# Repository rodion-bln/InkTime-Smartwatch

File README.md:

#  InkTime v6 - Smartwatch Project

**InkTime v6** este un ceas inteligent ultra-low-power, optimizat pentru eficiență și dimensiuni reduse. Proiectul utilizează un procesor nRF52840 și un ecran E-Ink de 1.54 inch, fiind capabil de o autonomie extinsă datorită managementului energetic avansat.

-----

## Diagrama Bloc a Sistemului

```mermaid
flowchart TD
    subgraph PCB_InkTime_v6 [InkTime v6 - 2D Layout Map]
        direction TB

        subgraph Top_Edge [Marginea de Sus - Alimentare]
            USB_C[Port USB-C]
            BAT_PADS[Pad-uri Baterie Li-Po]
            PMIC[Circuit Incarcare BQ25180]
        end

        %% Centrul Plăcii
        subgraph Center_Area [Nucleu Central]
            MCU[nRF52840 SoC]
            XTAL[Oscilatoare 32MHz / 32kHz]
        end

        subgraph Left_Side [Interfata Vizuala]
            DISPLAY_FPC[Conector Display FPC]
            V_REG[Regulator RT6160]
        end

        subgraph Right_Side [Comunicatii RF]
            ANT[Antena Chip Johanson]
            MATCH[Circuit Matching RF]
        end

        subgraph Bottom_Edge [Interfata Programare si Haptic]
            SWD[Pad-uri SWD / Tag-Connect]
            HAPTIC[Driver Haptic + Motor]
            TP_SDA[TP SDA]
            TP_SCL[TP SCL]
        end

        USB_C --> PMIC
        PMIC <--> BAT_PADS
        PMIC --> V_REG --> MCU
        
        MCU -- SPI --> DISPLAY_FPC
        MCU -- I2C --> HAPTIC
        MCU -- I2C --> TP_SDA
        MCU -- I2C --> TP_SCL
        
        MCU -- Traseu 50 Ohm --> MATCH --> ANT
        SWD <--> MCU
        XTAL --- MCU
    end

    %% Stiluri pentru a potrivi vizual cu imaginea
    style MCU fill:#d11,stroke:#333,stroke-width:2px,color:#fff
    style PCB_InkTime_v6 fill:#37474f,stroke:#fff,stroke-width:2px,color:#fff
    style ANT fill:#000,stroke:#f00,color:#fff
    style USB_C fill:#999,stroke:#333
    style SWD fill:#fbc02d,stroke:#333
    style DISPLAY_FPC fill:#546e7a,stroke:#fff,color:#fff
```
-----

## Bill of Materials (BOM) - Componente Cheie

| Componentă | Descriere | Pachet | Link (CSE/SnapEDA) |
| :--- | :--- | :--- | :--- |
| **nRF52840** | Microcontroller BT 5.0 | aQFN-73 | [SnapEDA](https://www.snapeda.com/parts/NRF52840-QIAA-R/Nordic%20Semiconductor/view-part/) |
| **BQ25180** | Battery Charger IC | WLCSP-8 | [CSE](https://componentsearchengine.com/search?term=BQ25180) |
| **MAX17048** | Fuel Gauge (ModelGauge) | WLP-8 | [CSE](https://componentsearchengine.com/search?term=MAX17048) |
| **RT6160** | Buck-Boost Converter | WL-CSP-15 | [CSE](https://componentsearchengine.com/search?term=RT6160) |
| **DRV2605L** | Haptic Driver | VSSOP-10 | [CSE](https://componentsearchengine.com/search?term=DRV2605L) |
| **E-Paper Display Connector** | 1.54" V2 Display | FPC-24 | [CSE](https://componentsearchengine.com/search?term=5034802400) |
| **2450AT** | Antenă Ceramică Chip | 3.2x1.6mm | [CSE](https://componentsearchengine.com/search?term=2450AT18B100E) |

-----

## Descrierea Funcționalității Hardware

### 1\. Sistemul de Procesare (nRF52840)

Utilizăm arhitectura **ARM Cortex-M4F** la **$64\text{ MHz}$**. Alegerea acestui MCU a fost dictată de suportul nativ pentru **USB 2.0** și stack-ul Bluetooth de joasă energie. Comunică cu display-ul prin **SPI** (frecvență de până la $8\text{ MHz}$) și cu restul perifericelor prin **I2C**.

### 2\. Managementul Energiei (Power Path)

  * **Buck-Boost (RT6160):** Asigură o tensiune stabilă de **$3.3\text{V}$** indiferent dacă bateria este la $4.2\text{V}$ (plină) sau scade la $3.0\text{V}$. Acest lucru previne "flicărirea" ecranului sau deconectarea Bluetooth-ului.
  * **Fuel Gauge (MAX17048):** Monitorizează starea bateriei fără a necesita o rezistență de șunt, economisind spațiu și energie.
  * **Consum estimat:**
      * **Deep Sleep:** $\approx 2.5\text{ µA}$
      * **Refresh Ecran:** $\approx 25\text{ mA}$ (timp de 2 secunde)
      * **Autonomie (150mAh):** Aproximativ **18 zile** (cu 10 refresh-uri/zi și conexiune BT intermitentă).

### 3\. Interfață și Feedback

  * **E-Paper:** Tehnologia bi-stabilă permite păstrarea imaginii pe ecran cu **consum zero**.
  * **Haptic Driver (DRV2605L):** Oferă feedback tactil configurabil prin I2C.

-----

## Maparea Pinilor nRF52840

| Pin MCU | Funcție | Componentă | Explicație |
| :--- | :--- | :--- | :--- |
| **P0.26 / P0.27** | SDA / SCL | I2C Bus | Magistrală comună pentru MAX17048, BQ25180, DRV2605. |
| **P0.20** | SCK | SPI Display | Ceasul pentru transferul datelor de imagine. |
| **P0.22** | MOSI | SPI Display | Master Out Slave In - datele către controllerul ecranului. |
| **P0.24** | CS | SPI Display | Chip Select pentru activarea ecranului. |
| **P0.15** | BUSY | Input | Semnal de la ecran către MCU când operația de refresh e gata. |
| **P0.00 / P0.01** | XL1 / XL2 | Cristal 32kHz | Furnizează baza de timp precisă pentru RTC în sleep. |
| **VBUS / D+ / D-** | USB Data | USB-C | Programare, debug și încărcare baterie. |

-----

## Design Log & Decizii de Implementare

### 1\. Decizia privind Vias (Overlap la Pini)

În zona procesorului **nRF52840 (aQFN73)**, am acceptat mici **erori de overlap (suprapuneri)** între vias și pad-urile pinilor.

  * **Justificare:** Densitatea extremă a pinilor nu permitea rutarea standard fără a trece la tehnologii costisitoare de tip *Blind/Buried Vias* sau *Via-in-Pad*. Suprapunerea a fost calculată pentru a asigura continuitatea electrică fără a compromite integritatea structurală a pad-ului în timpul lipirii industriale. Aceasta a permis rutarea pe un PCB standard de **4 straturi**.

### 2\. Integritatea Semnalului (Stackup)

  * S-a implementat un **plan de masă solid (Solid GND)** pe Layer 15.
  * **Decizie:** Nu s-au rutat semnale prin Layer 15 pentru a evita crearea de "antene" accidentale și pentru a oferi o cale de întoarcere curată pentru semnalul RF de $2.4\text{GHz}$.

### 3\. Mecanică și 3D

  * Utilizarea conectorului **TC2030 (Tag-Connect)** pentru a elimina mufa de programare de pe placă, reducând înălțimea totală a ceasului cu **$2\text{ mm}$**.

-----

## Structura Proiectului

  * `/Hardware`: Scheme (.fsch) și Board (.fbrd).
  * `/Manufacturing`: Gerbers.zip
  * `/Mechanical`: Fișier STEP și Carcasa.
  * `/Images`: Randări

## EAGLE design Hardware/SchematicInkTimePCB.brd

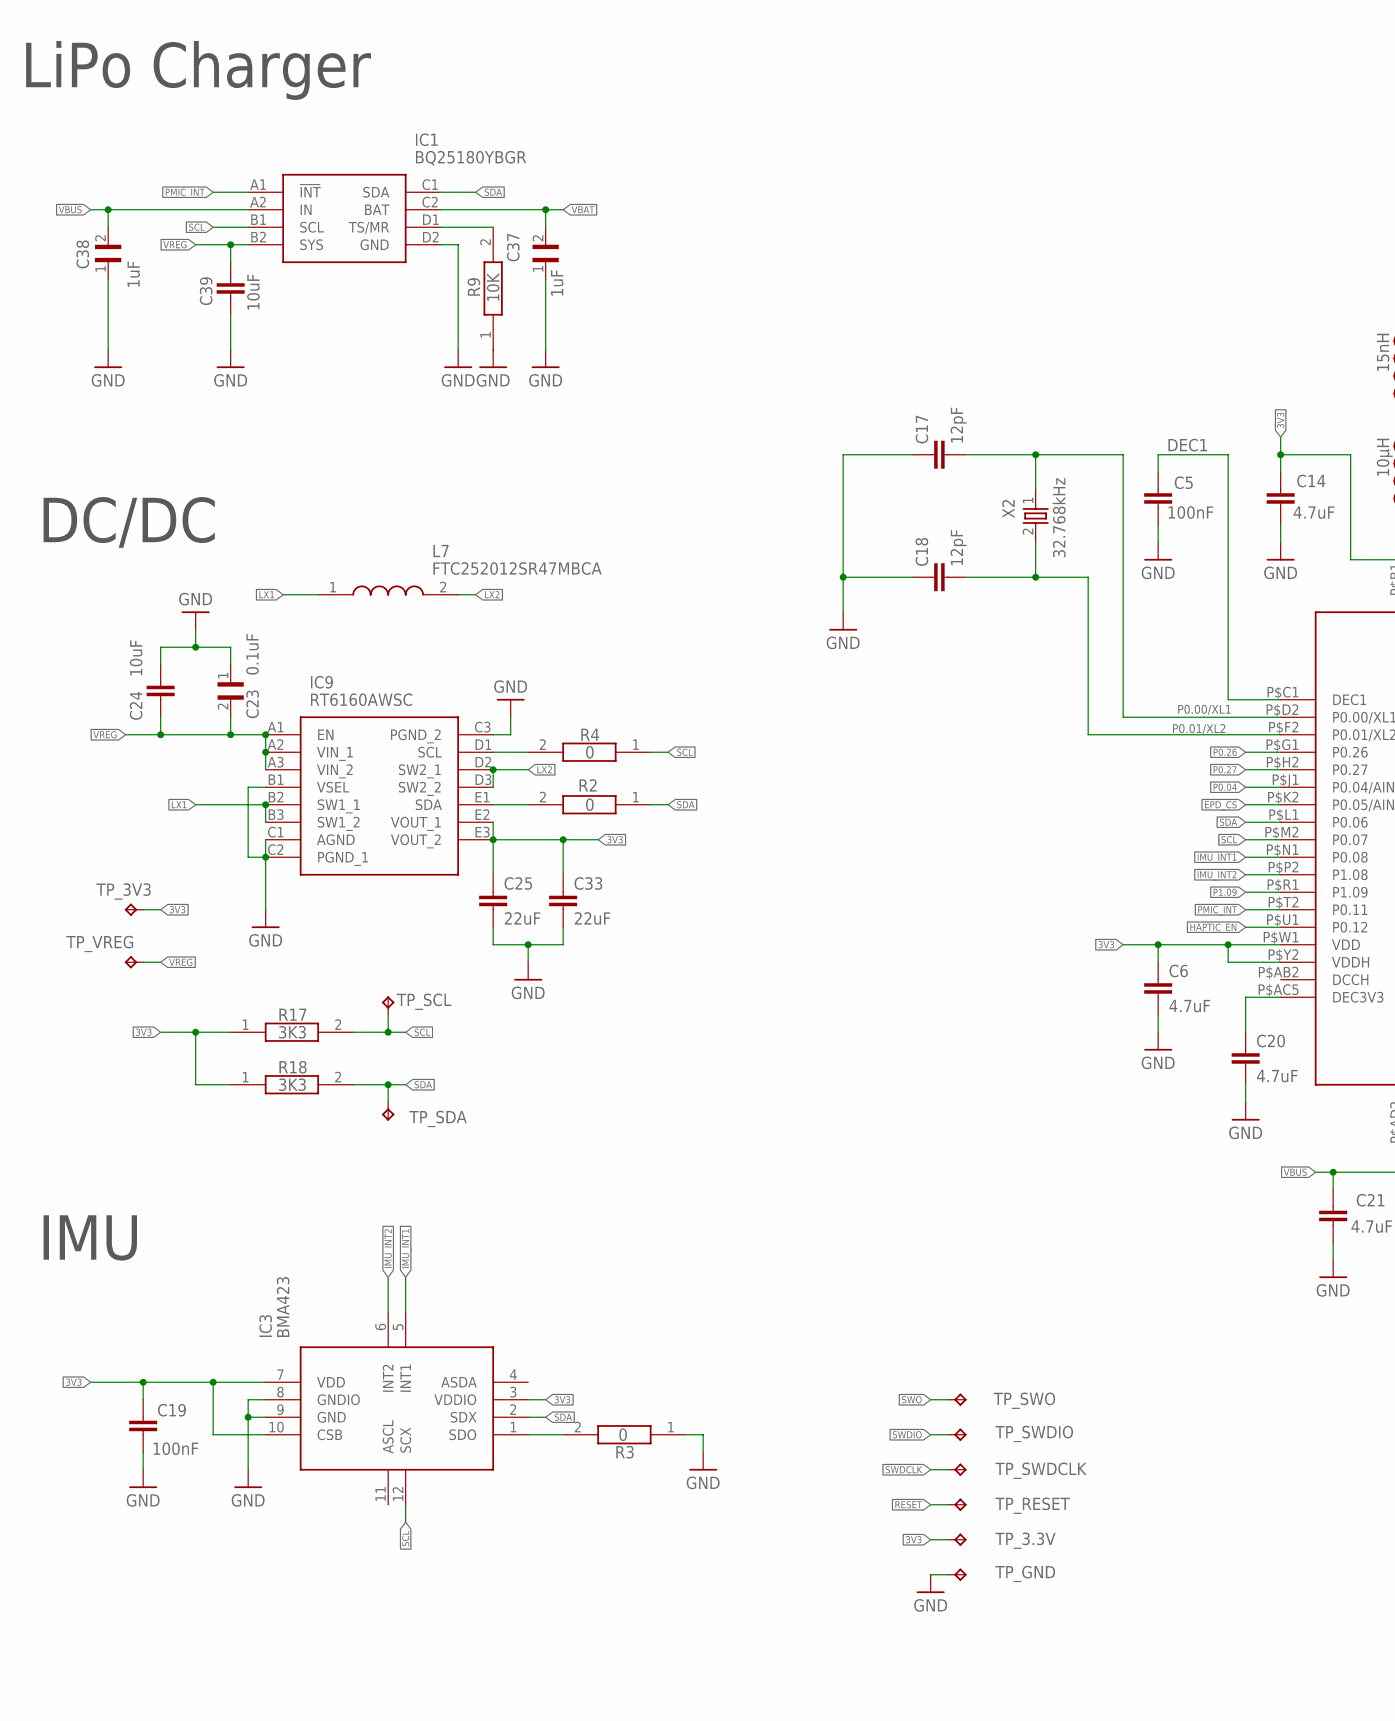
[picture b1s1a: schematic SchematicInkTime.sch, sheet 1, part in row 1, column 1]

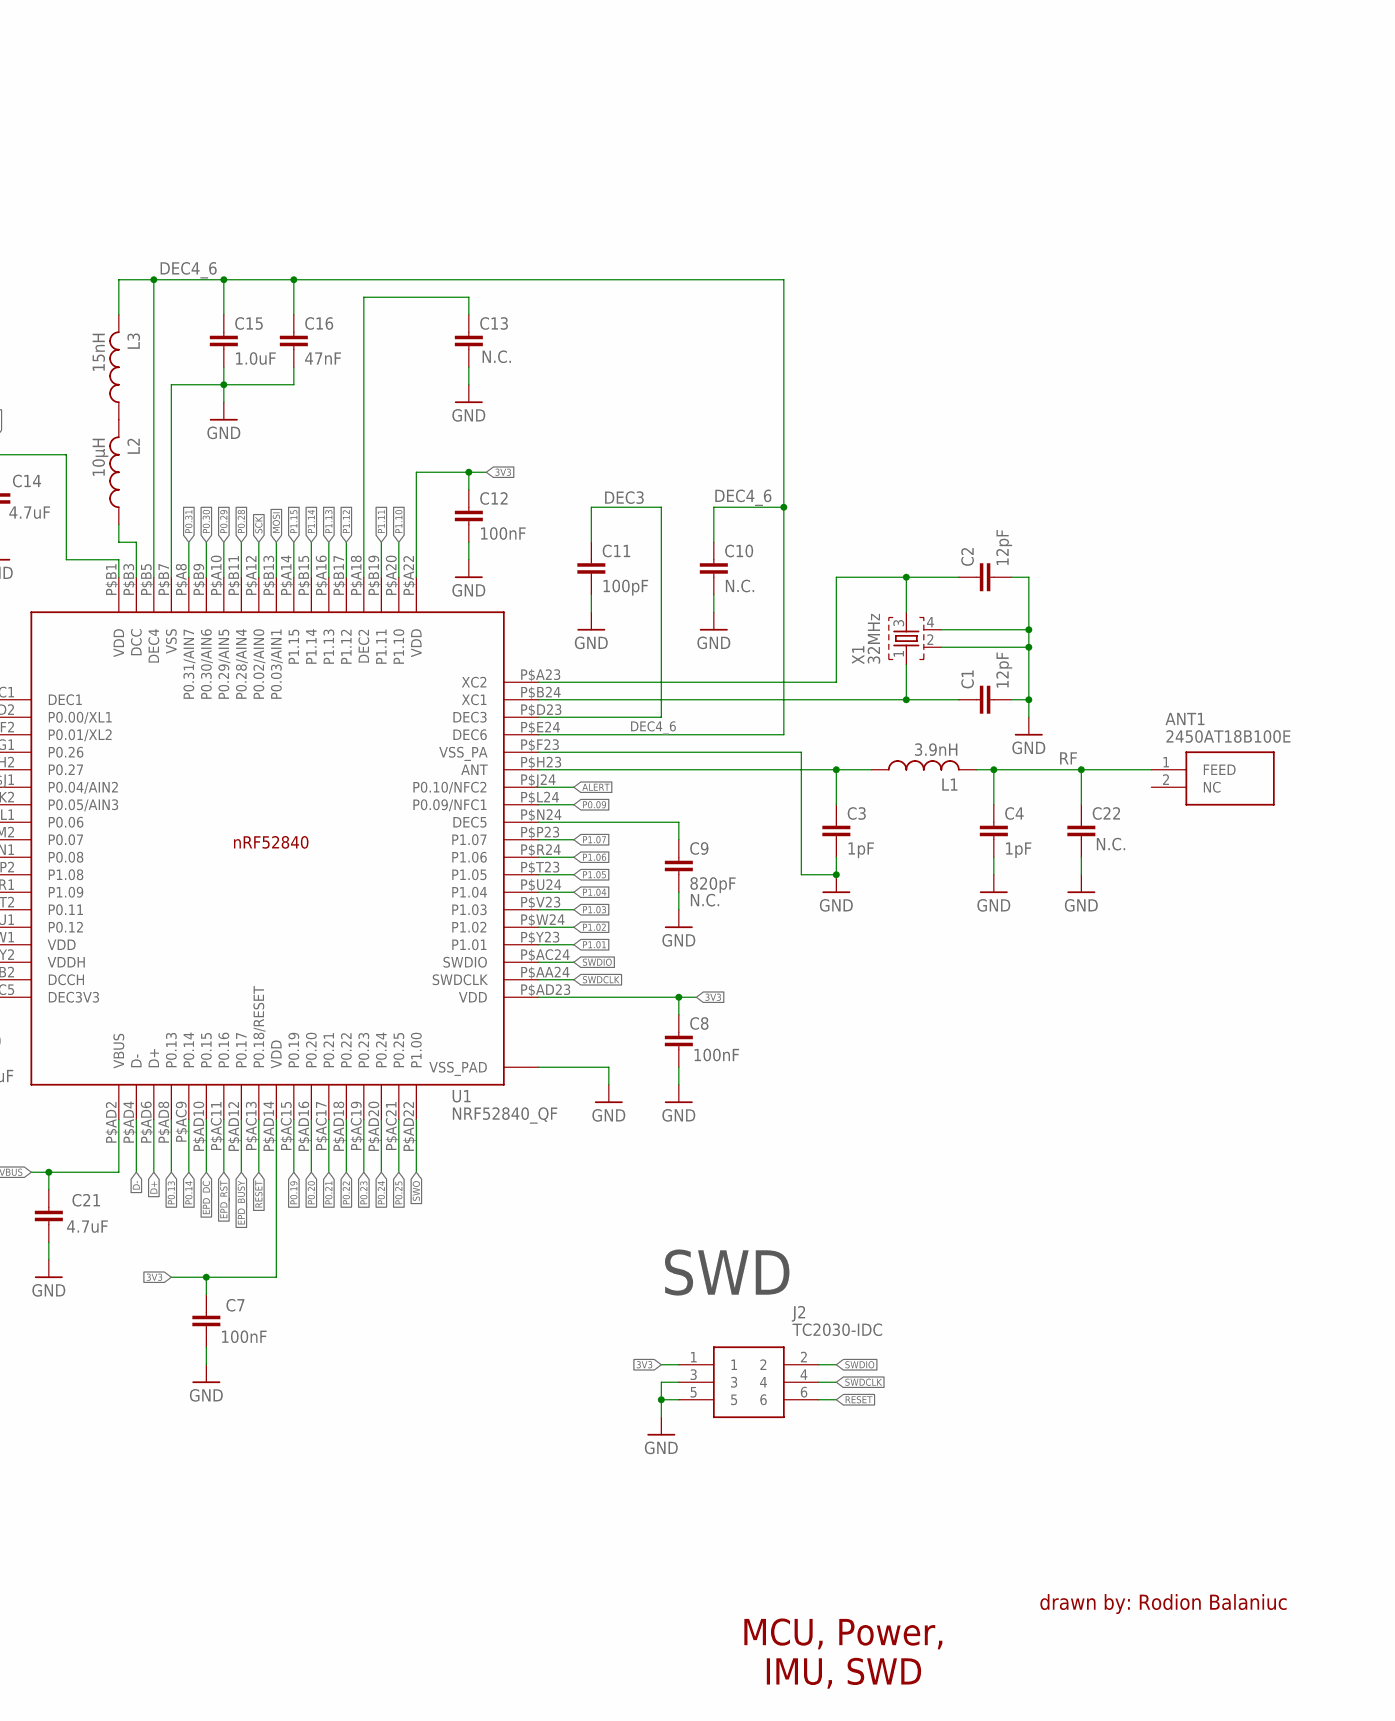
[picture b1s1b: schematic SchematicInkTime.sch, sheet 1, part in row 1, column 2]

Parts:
ANT1: 2450AT18B100E; 2450AT18B100E_ANTC3216X140N
C1, C2, C17, C18: 12pF; NORDIC_NRF_3_RESC0201_L
C3, C4: 1pF; NORDIC_NRF_3_RESC0201_L
C5, C7, C8, C12, C19: 100nF; NORDIC_NRF_3_RESC0201_L
C6, C14, C20, C21: 4.7uF; ESP32_C6_LIBRARY_1_ESP32_WROVER_EAGLE-LTSPICE_C0402
C9: 820pF; NORDIC_NRF_3_RESC0201_L
C10, C13, C22: N.C.; NORDIC_NRF_3_RESC0201_L
C11: 100pF; NORDIC_NRF_3_RESC0201_L
C15: 1.0uF; ESP32_C6_LIBRARY_1_ESP32_WROVER_EAGLE-LTSPICE_C0402
C16: 47nF; NORDIC_NRF_3_RESC0201_L
C23: 0.1uF; GRM011R60J152KE01L_2_CAPC0201X13N
C24, C39: 10uF; ESP32_C6_LIBRARY_1_ESP32_WROVER_EAGLE-LTSPICE_C0402
C25, C33: 22uF; ESP32_C6_LIBRARY_1_ESP32_WROVER_EAGLE-LTSPICE_C0402
C37, C38: 1uF; GRM011R60J152KE01L_2_CAPC0201X13N
IC1: BQ25180YBGR; BQ25180YBGR_BGA8C40P2X4_100X155X50
IC3: BMA423; BMA423_BMA423
IC9: RT6160AWSC; RT6160AWSC_BGA15C40P3X5_140X230X60
J2: TC2030-IDC; TC2030-IDC_TC2030IDC
L1: 3.9nH; NORDIC_NRF_2_RESC0402_L
L2: 10µH; NORDIC_NRF_2_RESC0402_L
L3: 15nH; NORDIC_NRF_2_RESC0402_L
L7: FTC252012SR47MBCA; MLP2016SR47MT0S1_INDC2016X100N
R2, R3, R4: 0; CPF0201D7K68C1_0201
R9: 10K; CPF0201D7K68C1_0201
R17, R18: 3K3; ERA-1AEB3401C_0201
TP_3.3V, TP_3V3: HECTOR_WATCH_1_TPTP20R; HECTOR_WATCH_1_TP20R
TP_GND: HECTOR_WATCH_1_TPTP20R; HECTOR_WATCH_1_TP20R
TP_RESET: HECTOR_WATCH_1_TPTP20R; HECTOR_WATCH_1_TP20R
TP_SCL: HECTOR_WATCH_1_TPTP20R; HECTOR_WATCH_1_TP20R
TP_SDA: HECTOR_WATCH_1_TPTP20R; HECTOR_WATCH_1_TP20R
TP_SWDCLK: HECTOR_WATCH_1_TPTP20R; HECTOR_WATCH_1_TP20R
TP_SWDIO: HECTOR_WATCH_1_TPTP20R; HECTOR_WATCH_1_TP20R
TP_SWO: HECTOR_WATCH_1_TPTP20R; HECTOR_WATCH_1_TP20R
TP_VREG: HECTOR_WATCH_1_TPTP20R; HECTOR_WATCH_1_TP20R
U1: NRF52840_QF; NORDIC_NRF_4_AQFN50P700X700X85_HS-74N
X1: 32MHz; NORDIC_NRF_BT-XTAL_2016_N
X2: 32.768kHz; NORDIC_NRF_1_XTAL_3215_N

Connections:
3V3: C6.1, C7.1, C8.1, C12.1, C14.1, C19.1, C25.1, C33.1, IC3.3 (VDDIO), IC3.7 (VDD), IC3.10 (CSB), IC9.E2 (VOUT_1), IC9.E3 (VOUT_2), J2.1, R17.1, R18.1, TP_3.3V.TP, TP_3V3.TP, U1.P$A22 (VDD), U1.P$AD14 (VDD), U1.P$AD23 (VDD), U1.P$B1 (VDD), U1.P$W1 (VDD), U1.P$Y2 (VDDH); also elsewhere on the board
ALERT: U1.P$J24 (P0.10/NFC2); also elsewhere on the board
D+: U1.P$AD6 (D+); also elsewhere on the board
D-: U1.P$AD4 (D-); also elsewhere on the board
DEC1: C5.1, U1.P$C1 (DEC1)
DEC3: C11.1, U1.P$D23 (DEC3)
DEC4_6: C10.1, C15.1, C16.1, L3.2, U1.P$B5 (DEC4), U1.P$E24 (DEC6)
EPD_BUSY: U1.P$AD12 (P0.17); also elsewhere on the board
EPD_CS: U1.P$K2 (P0.05/AIN3); also elsewhere on the board
EPD_DC: U1.P$AD10 (P0.15); also elsewhere on the board
EPD_RST: U1.P$AC11 (P0.16); also elsewhere on the board
GND: C1.2, C2.2, C3.2, C4.2, C5.2, C6.2, C7.2, C8.2, C9.2, C10.2, C11.2, C12.2, C13.2, C14.2, C15.2, C16.2, C17.1, C18.1, C19.2, C20.2, C21.2, C22.2, C23.1, C24.1, C25.2, C33.2, C37.1, C38.1, C39.2, IC1.D2 (GND), IC3.8 (GNDIO), IC3.9 (GND), IC9.B1 (VSEL), IC9.C1 (AGND), IC9.C2 (PGND_1), IC9.C3 (PGND_2), J2.3, J2.5, R3.1, R9.1, TP_GND.TP, U1.P$74 (VSS_PAD), U1.P$75 (VSS_PAD), U1.P$76 (VSS_PAD), U1.P$77 (VSS_PAD), U1.P$78 (VSS_PAD), U1.P$79 (VSS_PAD), U1.P$80 (VSS_PAD), U1.P$81 (VSS_PAD), U1.P$82 (VSS_PAD), U1.P$83 (VSS_PAD), U1.P$84 (VSS_PAD), U1.P$85 (VSS_PAD), U1.P$86 (VSS_PAD), U1.P$87 (VSS_PAD), U1.P$88 (VSS_PAD), U1.P$89 (VSS_PAD), U1.P$90 (VSS_PAD), U1.P$B7 (VSS), U1.P$F23 (VSS_PA), X1.2, X1.4; also elsewhere on the board
HAPTIC_EN: U1.P$U1 (P0.12); also elsewhere on the board
IMU_INT1: IC3.5 (INT1), U1.P$N1 (P0.08)
IMU_INT2: IC3.6 (INT2), U1.P$P2 (P1.08)
LX1: IC9.B2 (SW1_1), IC9.B3 (SW1_2), L7.1
LX2: IC9.D2 (SW2_1), IC9.D3 (SW2_2), L7.2
MOSI: U1.P$B13 (P0.03/AIN1); also elsewhere on the board
unnamed: IC1.D1 (TS/MR), R9.2
unnamed: IC9.D1 (SCL), R4.2
unnamed: IC9.E1 (SDA), R2.2
unnamed: IC3.1 (SDO), R3.2
unnamed: C20.1, U1.P$AC5 (DEC3V3)
unnamed: C13.1, U1.P$A18 (DEC2)
unnamed: L2.2, L3.1
unnamed: L2.1, U1.P$B3 (DCC)
unnamed: C2.1, U1.P$A23 (XC2), X1.3
unnamed: C3.1, L1.1, U1.P$H23 (ANT)
unnamed: C1.1, U1.P$B24 (XC1), X1.1
unnamed: C9.1, U1.P$N24 (DEC5)
P0.00/XL1: C17.2, U1.P$D2 (P0.00/XL1), X2.1
P0.01/XL2: C18.2, U1.P$F2 (P0.01/XL2), X2.2
P0.04: U1.P$J1 (P0.04/AIN2)
P0.09: U1.P$L24 (P0.09/NFC1)
P0.13: U1.P$AD8 (P0.13); also elsewhere on the board
P0.14: U1.P$AC9 (P0.14); also elsewhere on the board
P0.19: U1.P$AC15 (P0.19)
P0.20: U1.P$AD16 (P0.20)
P0.21: U1.P$AC17 (P0.21)
P0.22: U1.P$AD18 (P0.22)
P0.23: U1.P$AC19 (P0.23)
P0.24: U1.P$AD20 (P0.24)
P0.25: U1.P$AC21 (P0.25)
P0.26: U1.P$G1 (P0.26)
P0.27: U1.P$H2 (P0.27)
P0.28: U1.P$B11 (P0.28/AIN4)
P0.29: U1.P$A10 (P0.29/AIN5)
P0.30: U1.P$B9 (P0.30/AIN6)
P0.31: U1.P$A8 (P0.31/AIN7)
P1.01: U1.P$Y23 (P1.01); also elsewhere on the board
P1.02: U1.P$W24 (P1.02); also elsewhere on the board
P1.03: U1.P$V23 (P1.03)
P1.04: U1.P$U24 (P1.04)
P1.05: U1.P$T23 (P1.05)
P1.06: U1.P$R24 (P1.06)
P1.07: U1.P$P23 (P1.07)
P1.09: U1.P$R1 (P1.09)
P1.10: U1.P$A20 (P1.10)
P1.11: U1.P$B19 (P1.11)
P1.12: U1.P$B17 (P1.12)
P1.13: U1.P$A16 (P1.13)
P1.14: U1.P$B15 (P1.14)
P1.15: U1.P$A14 (P1.15)
PMIC_INT: IC1.A1 (!INT), U1.P$T2 (P0.11)
RESET: J2.6, TP_RESET.TP, U1.P$AC13 (P0.18/RESET)
RF: ANT1.1 (FEED), C4.1, C22.1, L1.2
SCK: U1.P$A12 (P0.02/AIN0); also elsewhere on the board
SCL: IC1.B1 (SCL), IC3.12 (SCX), R4.1, R17.2, TP_SCL.TP, U1.P$M2 (P0.07); also elsewhere on the board
SDA: IC1.C1 (SDA), IC3.2 (SDX), R2.1, R18.2, TP_SDA.TP, U1.P$L1 (P0.06); also elsewhere on the board
SWDCLK: J2.4, TP_SWDCLK.TP, U1.P$AA24 (SWDCLK)
SWDIO: J2.2, TP_SWDIO.TP, U1.P$AC24 (SWDIO)
SWO: TP_SWO.TP, U1.P$AD22 (P1.00)
VBAT: C37.2, IC1.C2 (BAT); also elsewhere on the board
VBUS: C21.1, C38.2, IC1.A2 (IN), U1.P$AD2 (VBUS); also elsewhere on the board
VREG: C23.2, C24.2, C39.1, IC1.B2 (SYS), IC9.A1 (EN), IC9.A2 (VIN_1), IC9.A3 (VIN_2), TP_VREG.TP

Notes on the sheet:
MCU, Power, IMU, SWD
LiPo Charger
DC/DC
IMU
drawn by: Rodion Balaniuc
SWD

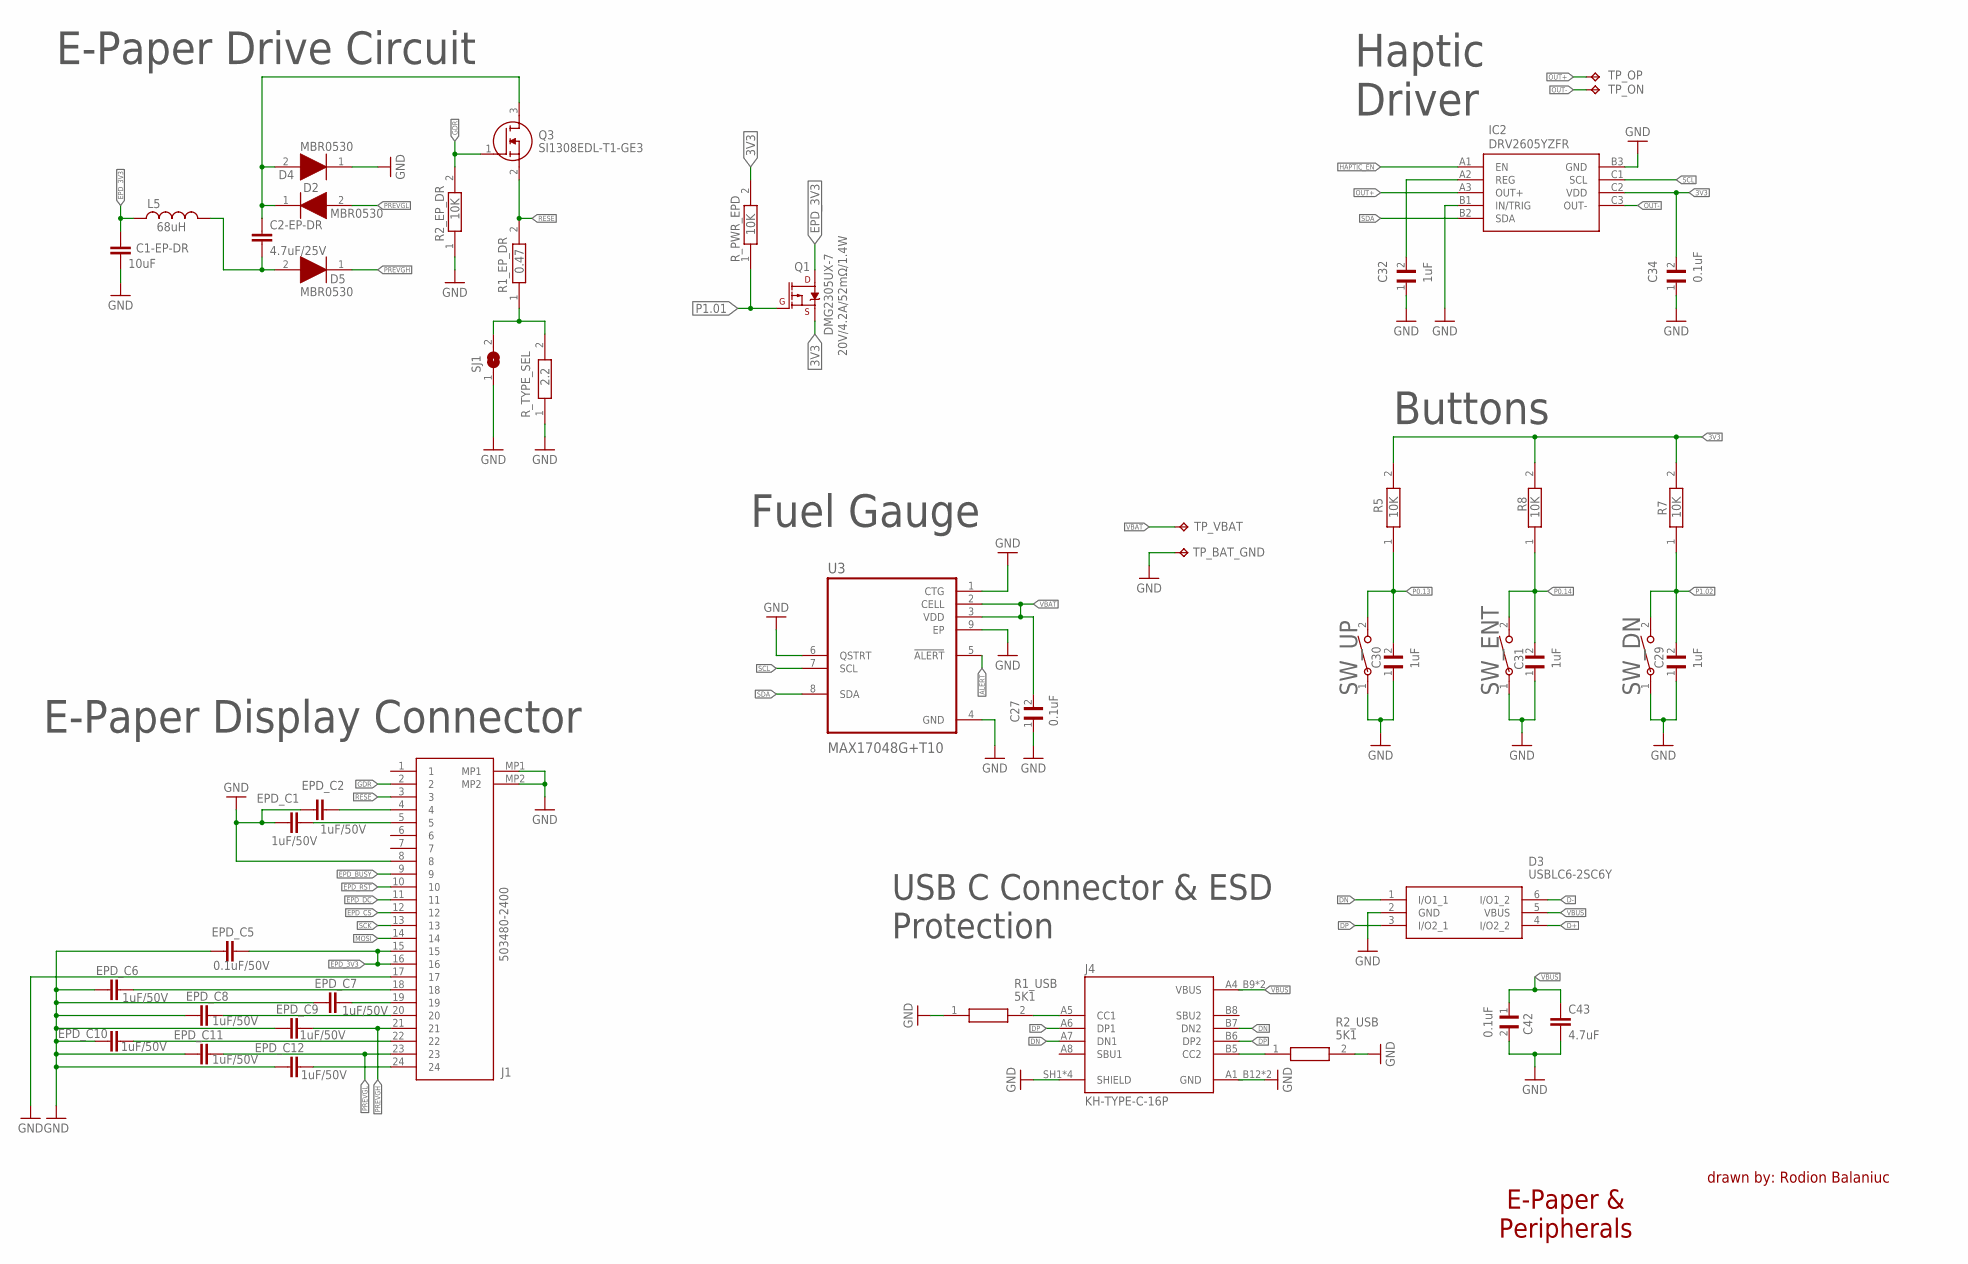
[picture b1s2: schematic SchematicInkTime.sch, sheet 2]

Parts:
C1-EP-DR: 10uF; ESP32_C6_LIBRARY_1_ESP32_WROVER_EAGLE-LTSPICE_C0402
C2-EP-DR: 4.7uF/25V; ESP32_C6_LIBRARY_1_ESP32_WROVER_EAGLE-LTSPICE_C0402
C27, C34, C42: 0.1uF; GRM011R60J152KE01L_2_CAPC0201X13N
C29, C30, C31, C32: 1uF; GRM011R60J152KE01L_2_CAPC0201X13N
C43: 4.7uF; ESP32_C6_LIBRARY_1_ESP32_WROVER_EAGLE-LTSPICE_C0402
D2, D4, D5: MBR0530; ESP32_C6_LIBRARY_5_SOD3716X135N
D3: USBLC6-2SC6Y; ESP32_C6_LIBRARY_3_SOT95P280X145-6N
EPD_C1, EPD_C2, EPD_C6, EPD_C7, EPD_C8, EPD_C9, EPD_C10, EPD_C11, EPD_C12: 1uF/50V; ESP32_C6_LIBRARY_1_ESP32_WROVER_EAGLE-LTSPICE_C0402
EPD_C5: 0.1uF/50V; ESP32_C6_LIBRARY_1_ESP32_WROVER_EAGLE-LTSPICE_C0402
IC2: DRV2605YZFR; DRV2605YZFR_BGA9C50P3X3_144X144X62
J1: 503480-2400; 503480-2400_5034802400
J4: KH-TYPE-C-16P; KH-TYPE-C-16P_KINGHELM_KH-TYPE-C-16P
L5: 68uH; NORDIC_NRF_2_RESC0402_L
Q1: 20V/4.2A/52mΩ/1.4W; ESP32_C6_LIBRARY_4_ESP32_C6_LIBRARY_4_ESP32_C6_LIBRARY_4_ES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
Q3: SI1308EDL-T1-GE3; ESP32_C6_LIBRARY_6_SOT65P210X110-3N
R1_EP_DR: 0.47; CPF0201D7K68C1_0201
R1_USB, R2_USB: 5K1; CPF0201D7K68C1_0201
R2_EP_DR, R5, R7, R8: 10K; CPF0201D7K68C1_0201
R_PWR_EPD: 10K; CPF0201D7K68C1_0201
R_TYPE_SEL: 2.2; CPF0201D7K68C1_0201
SJ1: ESP32_C6_LIBRARY_7_JUMPER_SJ
SW_DN: 2025-10-22_07-23-44_LIBRARY_EVP-AKE31ASW_EVP-AKE3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; 2025-10-22_07-23-44_LIBRARY_SW_EVP-AKE31A_PAN
SW_ENT: 2025-10-22_07-23-44_LIBRARY_EVP-AKE31ASW_EVP-AKE3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; 2025-10-22_07-23-44_LIBRARY_SW_EVP-AKE31A_PAN
SW_UP: 2025-10-22_07-23-44_LIBRARY_EVP-AKE31ASW_EVP-AKE3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; 2025-10-22_07-23-44_LIBRARY_SW_EVP-AKE31A_PAN
TP_BAT_GND: HECTOR_WATCH_1_TPTP20R; HECTOR_WATCH_1_TP20R
TP_ON: HECTOR_WATCH_1_TPTP20R; HECTOR_WATCH_1_TP20R
TP_OP: HECTOR_WATCH_1_TPTP20R; HECTOR_WATCH_1_TP20R
TP_VBAT: HECTOR_WATCH_1_TPTP20R; HECTOR_WATCH_1_TP20R
U3: MAX17048G+T10; ESP32_C6_LIBRARY_SON50P200X200X80-9N

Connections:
3V3: C34.2, IC2.C2 (VDD), Q1.2 (S), R5.2, R7.2, R8.2, R_PWR_EPD.2; also elsewhere on the board
ALERT: U3.5 (!ALERT); also elsewhere on the board
D+: D3.4 (I/O2_2); also elsewhere on the board
D-: D3.6 (I/O1_2); also elsewhere on the board
DN: D3.1 (I/O1_1), J4.A7 (DN1), J4.B7 (DN2)
DP: D3.3 (I/O2_1), J4.A6 (DP1), J4.B6 (DP2)
EPD_3V3: C1-EP-DR.1, EPD_C5.2, J1.15, J1.16, L5.1, Q1.3 (D)
EPD_BUSY: J1.9; also elsewhere on the board
EPD_CS: J1.12; also elsewhere on the board
EPD_DC: J1.11; also elsewhere on the board
EPD_RST: J1.10; also elsewhere on the board
GDR: J1.2, Q3.1 (G), R2_EP_DR.2
GND: C1-EP-DR.2, C27.1, C29.1, C30.1, C31.1, C32.1, C34.1, C42.2, C43.2, D3.2 (GND), D4.1 (K), EPD_C1.1, EPD_C2.1, EPD_C5.1, EPD_C6.1, EPD_C7.1, EPD_C8.1, EPD_C9.1, EPD_C10.1, EPD_C11.1, EPD_C12.1, IC2.B1 (IN/TRIG), IC2.B3 (GND), J1.8, J1.17, J1.MP1, J1.MP2, J4.A1_B12 (GND), J4.A12_B1 (GND), J4.SH1 (SHIELD), J4.SH2 (SHIELD), J4.SH3 (SHIELD), J4.SH4 (SHIELD), R1_USB.1, R2_EP_DR.1, R2_USB.2, R_TYPE_SEL.1, SJ1.1, SW_DN.1, SW_ENT.1, SW_UP.1, TP_BAT_GND.TP, U3.1 (CTG), U3.4 (GND), U3.6 (QSTRT), U3.9 (EP); also elsewhere on the board
HAPTIC_EN: IC2.A1 (EN); also elsewhere on the board
MOSI: J1.14; also elsewhere on the board
unnamed: C32.2, IC2.A2 (REG)
unnamed: J4.A5 (CC1), R1_USB.2
unnamed: C2-EP-DR.2, D5.2 (A), L5.2
unnamed: C2-EP-DR.1, D2.1 (K), D4.2 (A), Q3.3 (D)
unnamed: EPD_C2.2, J1.4
unnamed: EPD_C1.2, J1.5
unnamed: EPD_C6.2, J1.18
unnamed: EPD_C7.2, J1.19
unnamed: R1_EP_DR.1, R_TYPE_SEL.2, SJ1.2
unnamed: EPD_C8.2, J1.20
unnamed: EPD_C9.2, J1.21
unnamed: EPD_C10.2, J1.22
unnamed: J4.B5 (CC2), R2_USB.1
OUT+: IC2.A3 (OUT+), TP_OP.TP
OUT-: IC2.C3 (OUT-), TP_ON.TP
P0.13: C30.2, R5.1, SW_UP.2; also elsewhere on the board
P0.14: C31.2, R8.1, SW_ENT.2; also elsewhere on the board
P1.01: Q1.1 (G), R_PWR_EPD.1; also elsewhere on the board
P1.02: C29.2, R7.1, SW_DN.2; also elsewhere on the board
PREVGH: D5.1 (K), EPD_C12.2, J1.24
PREVGL: D2.2 (A), EPD_C11.2, J1.23
RESE: J1.3, Q3.2 (S), R1_EP_DR.2
SCK: J1.13; also elsewhere on the board
SCL: IC2.C1 (SCL), U3.7 (SCL); also elsewhere on the board
SDA: IC2.B2 (SDA), U3.8 (SDA); also elsewhere on the board
VBAT: C27.2, TP_VBAT.TP, U3.2 (CELL), U3.3 (VDD); also elsewhere on the board
VBUS: C42.1, C43.1, D3.5 (VBUS), J4.A4_B9 (VBUS), J4.A9_B4 (VBUS); also elsewhere on the board

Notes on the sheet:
E-Paper & Peripherals
drawn by: Rodion Balaniuc
E-Paper Drive Circuit
Haptic Driver
E-Paper Display Connector
Fuel Gauge
Buttons
USB C Connector & ESD Protection

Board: 2 copper layers, 105 parts (0 on the bottom side), 70 nets, no tracks yet.

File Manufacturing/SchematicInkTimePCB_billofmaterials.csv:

Reference Designators;Quantity;Description;Package;Value;Manufacturer;Manufacturer Part Number;Vendor;Vendor Part Number;Top/Bottom;
;1;Board;Board;;;;;;;
ANT1;1;Antennas 2.45GHz ANTENNA;2450AT18B100E_ANTC3216X140N;2450AT18B100E;;;;;Top;
C1, C2, C17, C18;4;Generic chip capacitor;NORDIC_NRF_3_RESC0201_L;12pF;;;;;Top;
C1-EP-DR, C24, C39;3;CAPACITOR, European symbol;ESP32_WROVER_EAGLE-LTSPICE_C0402;10uF;;;;;Top;
C2-EP-DR;1;CAPACITOR, European symbol;ESP32_WROVER_EAGLE-LTSPICE_C0402;4.7uF/25V;;;;;Top;
C3, C4;2;Generic chip capacitor;NORDIC_NRF_3_RESC0201_L;1pF;;;;;Top;
C5, C7, C8, C12, C19;5;Generic chip capacitor;NORDIC_NRF_3_RESC0201_L;100nF;;;;;Top;
C6, C14, C20, C21, C43;5;CAPACITOR, European symbol;ESP32_WROVER_EAGLE-LTSPICE_C0402;4.7uF;;;;;Top;
C9;1;Generic chip capacitor;NORDIC_NRF_3_RESC0201_L;820pF;;;;;Top;
C10, C13, C22;3;Generic chip capacitor;NORDIC_NRF_3_RESC0201_L;N.C.;;;;;Top;
C11;1;Generic chip capacitor;NORDIC_NRF_3_RESC0201_L;100pF;;;;;Top;
C15;1;CAPACITOR, European symbol;ESP32_WROVER_EAGLE-LTSPICE_C0402;1.0uF;;;;;Top;
C16;1;Generic chip capacitor;NORDIC_NRF_3_RESC0201_L;47nF;;;;;Top;
C23, C27, C34, C42;4;Check availability;CAPC0201X13N;0.1uF;;;;;Top;
C25, C33;2;CAPACITOR, European symbol;ESP32_WROVER_EAGLE-LTSPICE_C0402;22uF;;;;;Top;
C29, C30, C31, C32, C37, C38;6;Check availability;CAPC0201X13N;1uF;;;;;Top;
D2, D4, D5;3;ON SEMICONDUCTOR - MBR0530 - DIODE, SCHOTTKY, 0.5A, 30V, SOD-123;SOD3716X135N;MBR0530;;;;;Top;
D3;1;Low Cap. ESD Protection Auto SOT-23-6 STMicroelectronics USBLC6-2SC6Y, Dual Uni-Directional TVS Diode Array, 6-Pin SOT-23;SOT95P280X145-6N;USBLC6-2SC6Y;;;;;Top;
EPD_C1, EPD_C2;2;CAPACITOR, European symbol;ESP32_WROVER_EAGLE-LTSPICE_C0402;1uF/50V ;;;;;Top;
EPD_C5;1;CAPACITOR, European symbol;ESP32_WROVER_EAGLE-LTSPICE_C0402;0.1uF/50V;;;;;Top;
EPD_C6, EPD_C7, EPD_C8, EPD_C9, EPD_C10, EPD_C11, EPD_C12;7;CAPACITOR, European symbol;ESP32_WROVER_EAGLE-LTSPICE_C0402;1uF/50V;;;;;Top;
IC1;1;Charger IC Lithium Ion/Polymer, Lithium Iron Phosphate 8-DSBGA (1.6x1.1);BQ25180YBGR_BGA8C40P2X4_100X155X50;BQ25180YBGR;;;;;Top;
IC2;1;Haptic Driver for ERM/LRA with Built-In Library and Smart Loop Architecture;DRV2605YZFR_BGA9C50P3X3_144X144X62;DRV2605YZFR;;;;;Top;
IC3;1;Accelerometers Triaxial low-g 12bit Acceleration Sensor;BMA423_BMA423;BMA423;;;;;Top;
IC9;1;Buck-Boost Regulator Positive Output Step-Up/Step-Down I2C DC-DC Controller IC 15-WL-CSP (BSC) (1.4x2.3);RT6160AWSC_BGA15C40P3X5_140X230X60;RT6160AWSC;;;;;Top;
J1;1;FFC & FPC Connectors 0.5mm FPC RA SMT Dual Contact 24Ckt;503480-2400_5034802400;503480-2400;;;;;Top;
J2;1;CABLE ADAPTER 6 POS;TC2030-IDC_TC2030IDC;TC2030-IDC;;;;;Top;
J4;1;Check availability;KINGHELM_KH-TYPE-C-16P;KH-TYPE-C-16P;;;;;Top;
L1;1;Generic chip inductor;NORDIC_NRF_2_RESC0402_L;3.9nH;;;;;Top;
L2;1;Generic chip inductor;NORDIC_NRF_2_RESC0402_L;10µH;;;;;Top;
L3;1;Generic chip inductor;NORDIC_NRF_2_RESC0402_L;15nH;;;;;Top;
L5;1;;ESP32_C6_LIBRARY_2_IND_4828-WE-TPC_WRE;65uH;;;;;Top;
L7;1;SMD / SMT Inductors (Coils), L=0.47?H, L x W x T :;MLP2016SR47MT0S1_INDC2016X100N;FTC252012SR47MBCA;;;;;Top;
Q1;1;P-channel MOSFETs;ESP32_WROVER_SPARKFUN-DISCRETESEMI_SOT23-3;20V/4.2A/52mΩ/1.4W;;;;;Top;
Q3;1;MOSFET N-Ch 30V 1.5A TrenchFET SC70 Vishay Si1308EDL-T1-GE3 N-channel MOSFET Transistor, 1.5 A, 30 V, 3-Pin SC-70;SOT65P210X110-3N;SI1308EDL-T1-GE3;;;;;Top;
R_PWR_EPD, R2_EP_DR, R5, R7, R8, R9;6;7.68k 0201 Thin Film Surface Mount Fixed Resistor +/-0.5% 0.031W CPF0201D7K68C1;CPF0201D7K68C1_0201;10K;;;;;Top;
R_TYPE_SEL;1;7.68k 0201 Thin Film Surface Mount Fixed Resistor +/-0.5% 0.031W CPF0201D7K68C1;CPF0201D7K68C1_0201;2.2;;;;;Top;
R1_EP_DR;1;7.68k 0201 Thin Film Surface Mount Fixed Resistor +/-0.5% 0.031W CPF0201D7K68C1;CPF0201D7K68C1_0201;0.47;;;;;Top;
R1_USB, R2_USB;2;7.68k 0201 Thin Film Surface Mount Fixed Resistor +/-0.5% 0.031W CPF0201D7K68C1;CPF0201D7K68C1_0201;5K1;;;;;Top;
R2, R3, R4;3;7.68k 0201 Thin Film Surface Mount Fixed Resistor +/-0.5% 0.031W CPF0201D7K68C1;CPF0201D7K68C1_0201;0;;;;;Top;
R17, R18;2;7.68k 0201 Thin Film Surface Mount Fixed Resistor +/-0.5% 0.031W CPF0201D7K68C1;R0201;3K3;;;;;Top;
SJ1;1;SMD solder JUMPER;JUMPER_SJ;;;;;;Top;
SW_DN, SW_ENT, SW_UP;3;;SW_EVP-AKE31A_PAN;2025-10-22_07-23-44_LIBRARY_EVP-AKE31ASW_EVP-AKE31A_PAN;;;;;Top;
TP_3.3V, TP_3V3, TP_BAT_GND, TP_GND, TP_ON, TP_OP, TP_RESET, TP_SCL, TP_SDA, TP_SWDCLK, TP_SWDIO, TP_SWO, TP_VBAT, TP_VREG;14;Test pad;HECTOR_WATCH_1_TP20R;HECTOR_WATCH_1_TPTP20R;;;;;Top;
U1;1;nRF52840;NORDIC_NRF_4_AQFN50P700X700X85_HS-74N;NRF52840_QF;;;;;Top;
U3;1;Check availability;SON50P200X200X80-9N;MAX17048G+T10;;;;;Top;
X1;1;;NORDIC_NRF_BT-XTAL_2016_N;32MHz;;;;;Top;
X2;1;;NORDIC_NRF_1_XTAL_3215_N;32.768kHz ;;;;;Top;

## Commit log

2026-04-10 Update README with project progress and details
    Added project status, current achievements, project structure, and technologies used.
2026-04-21 Revise README for InkTime v6 project overview
    Updated project details and implementation steps for InkTime v6 smartwatch.
2026-04-21 Rename gerbers.zip.zip to gerbers.zip
2026-04-21 README
2026-04-22 README
    Added a flowchart diagram of the system architecture using Mermaid syntax.

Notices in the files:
parts and their libraries:
InkTime_v5: COPYRIGHT: Copyright (C) 2025 Ultra Librarian. All rights reserved.
